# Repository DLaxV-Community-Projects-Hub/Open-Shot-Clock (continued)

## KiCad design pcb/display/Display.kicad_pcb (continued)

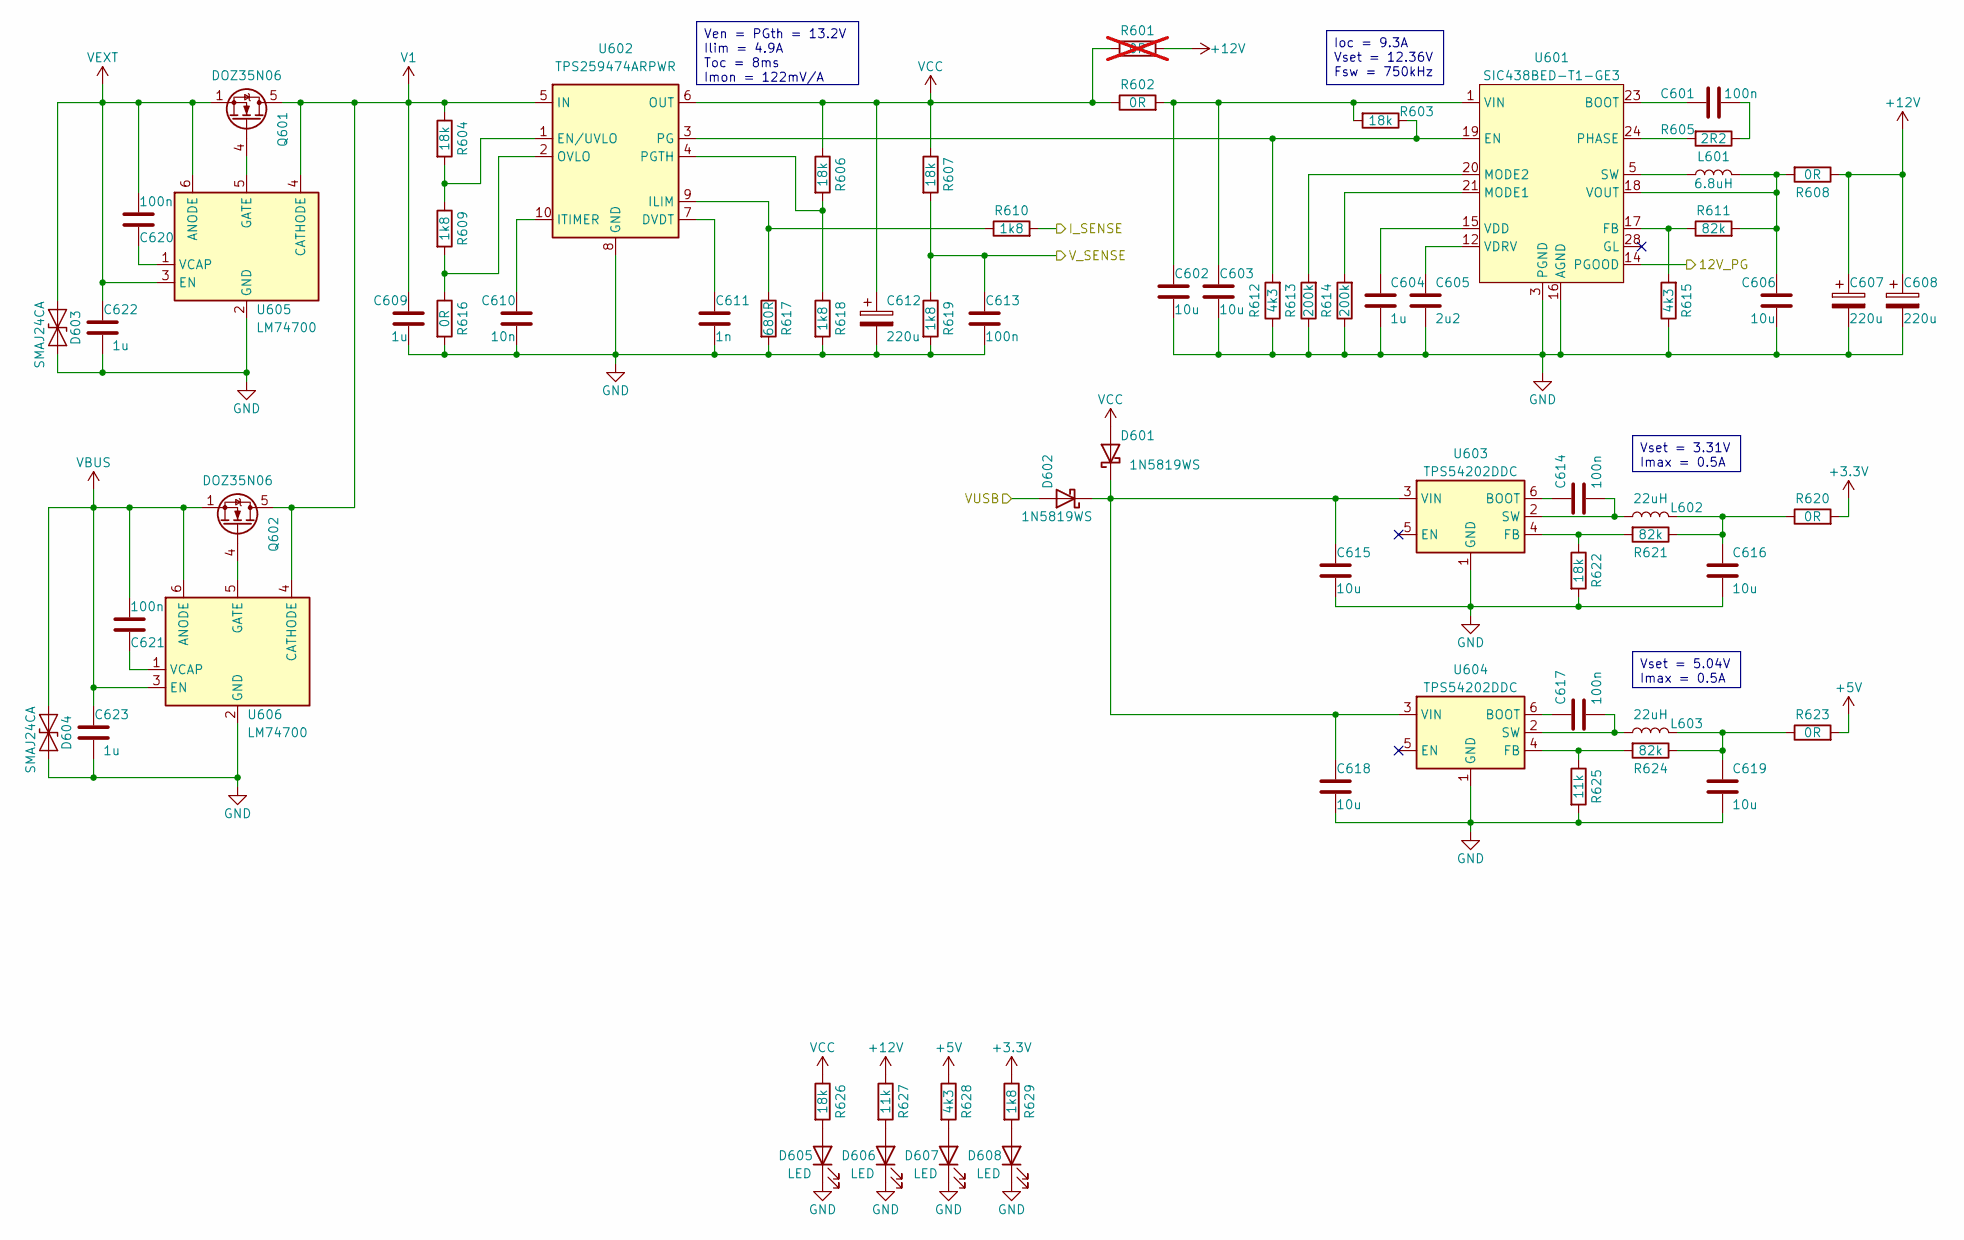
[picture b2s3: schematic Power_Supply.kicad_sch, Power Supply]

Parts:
C601, C613, C614, C617, C620, C621: 100n; C_0402_1005Metric; LCSC Part # C307331
C602, C603, C606, C615, C618: 10u; C_1206_3216Metric; LCSC Part # C13585
C604, C609, C622, C623: 1u; C_0603_1608Metric; LCSC Part # C15849
C605: 2u2; C_0603_1608Metric; LCSC Part # C23630
C607, C608, C612: 220u; CP_Elec_8x10; LCSC Part # C5246542
C610: 10n; C_0402_1005Metric; LCSC Part # C15195
C611: 1n; C_0402_1005Metric; LCSC Part # C1523
C616, C619: 10u; C_0603_1608Metric; LCSC Part # C19702
D601, D602: 1N5819WS; D_SOD-323; LCSC Part # C191023
D603, D604: SMAJ24CA; D_SMA; LCSC Part # C20883150
D605, D606, D607, D608: LED; LED_0603_1608Metric; LCSC Part # C2286
L601: 6.8uH; L_Bourns_SRP1050WA; LCSC Part # C32712978
L602, L603: 22uH; L_Changjiang_FNR4030S; LCSC Part # C206327
Q601, Q602: DOZ35N06; VSON-8_3.3x3.3mm_P0.65mm_Custom; LCSC Part # C36499167
R601: 0R; R_1206_3216Metric; not fitted
R602, R608: 0R; R_1206_3216Metric
R603, R604, R606, R607, R622, R626: 18k; R_0402_1005Metric
R605: 2R2; R_0402_1005Metric
R609, R610, R618, R619, R629: 1k8; R_0402_1005Metric
R611, R621, R624: 82k; R_0402_1005Metric
R612, R615, R628: 4k3; R_0402_1005Metric
R613, R614: 200k; R_0402_1005Metric
R616: 0R; R_0402_1005Metric
R617: 680R; R_0402_1005Metric
R620, R623: 0R; R_0603_1608Metric
R625, R627: 11k; R_0402_1005Metric
U601: SIC438BED-T1-GE3; Vishay_PowerPAK_MLP44-24L_ThermalVias; LCSC Part # C511430
U602: TPS259474ARPWR; RPW0010A_VQFN-HR-10; LCSC Part # C3662807
U603, U604: TPS54202DDC; SOT-23-6; LCSC Part # C191884
U605, U606: LM74700; SOT-23-6; LCSC Part # C2941042

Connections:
+3.3V: R620.2, R629.1; also elsewhere on the board
+5V: R623.2, R628.1; also elsewhere on the board
+12V: C607.1, C608.1, R601.2, R608.1, R627.1; also elsewhere on the board
/12V_PG: U601.14 (PGOOD); also elsewhere on the board
/I_SENSE: R610.2; also elsewhere on the board
/Power Supply/VUSB: D602.2 (A); also elsewhere on the board
/V_SENSE: C613.2, R607.2, R619.1; also elsewhere on the board
GND: C602.2, C603.2, C604.2, C605.2, C606.2, C607.2, C608.2, C609.1, C610.1, C611.1, C612.2, C613.1, C615.2, C616.2, C618.2, C619.2, C622.2, C623.2, D603.2 (A2), D604.2 (A2), D605.1 (K), D606.1 (K), D607.1 (K), D608.1 (K), R612.1, R613.1, R614.1, R615.1, R616.2, R617.2, R618.2, R619.2, R622.2, R625.2, U601.3 (PGND), U601.4 (PGND), U601.13 (PGND), U601.16 (AGND), U601.25 (AGND), U601.27 (PGND), U602.8 (GND), U603.1 (GND), U604.1 (GND), U605.2 (GND), U606.2 (GND); also elsewhere on the board
unnamed: C601.2, R605.1
unnamed: C616.1, L602.2, R620.1, R621.1
unnamed: C619.1, L603.2, R623.1, R624.1
unnamed: C615.1, C618.1, D601.1 (K), D602.1 (K), U603.3 (VIN), U604.3 (VIN)
unnamed: D605.2 (A), R626.2
unnamed: D606.2 (A), R627.2
unnamed: D607.2 (A), R628.2
unnamed: D608.2 (A), R629.2
unnamed: Q601.4 (G), U605.5 (GATE)
unnamed: Q602.4 (G), U606.5 (GATE)
unnamed: C601.1, U601.23 (BOOT)
unnamed: R603.1, R612.2, U601.19 (EN), U602.3 (PG)
unnamed: R611.1, R615.2, U601.17 (FB)
unnamed: R614.2, U601.21 (MODE1)
unnamed: R613.2, U601.20 (MODE2)
unnamed: R605.2, U601.24 (PHASE)
unnamed: C604.1, U601.15 (VDD)
unnamed: C605.1, U601.12 (VDRV)
unnamed: C606.1, L601.2, R608.2, R611.2, U601.18 (VOUT)
unnamed: C611.2, U602.7 (DVDT)
unnamed: R604.2, R609.1, U602.1 (EN/UVLO)
unnamed: R610.1, R617.1, U602.9 (ILIM)
unnamed: C610.2, U602.10 (ITIMER)
unnamed: R609.2, R616.1, U602.2 (OVLO)
unnamed: R606.2, R618.1, U602.4 (PGTH)
unnamed: C614.1, U603.6 (BOOT)
unnamed: R621.2, R622.1, U603.4 (FB)
unnamed: C614.2, L602.1, U603.2 (SW)
unnamed: C617.1, U604.6 (BOOT)
unnamed: R624.2, R625.1, U604.4 (FB)
unnamed: C617.2, L603.1, U604.2 (SW)
unnamed: C620.2, U605.1 (VCAP)
unnamed: C621.2, U606.1 (VCAP)
SW: L601.1, U601.5 (SW), U601.6 (SW), U601.7 (SW), U601.8 (SW), U601.9 (SW)
V1: C609.2, Q601.5 (D), Q602.5 (D), R604.1, U602.5 (IN), U605.4 (CATHODE), U606.4 (CATHODE)
VBUS: C621.1, C623.1, D604.1 (A1), Q602.1 (S), Q602.2 (S), Q602.3 (S), U606.3 (EN), U606.6 (ANODE); also elsewhere on the board
VCC: C612.1, D601.2 (A), R601.1, R602.1, R606.1, R607.1, R626.1, U602.6 (OUT); also elsewhere on the board
VEXT: C620.1, C622.1, D603.1 (A1), Q601.1 (S), Q601.2 (S), Q601.3 (S), U605.3 (EN), U605.6 (ANODE); also elsewhere on the board
VIN: C602.1, C603.1, R602.2, R603.2, U601.1 (VIN), U601.2 (VIN), U601.22 (VIN), U601.26 (VIN)

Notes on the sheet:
Vset = 3.31V Imax = 0.5A
Ven = PGth = 13.2V Ilim = 4.9A Toc = 8ms Imon = 122mV/A
Vset = 5.04V Imax = 0.5A
Ioc = 9.3A Vset = 12.36V Fsw = 750kHz

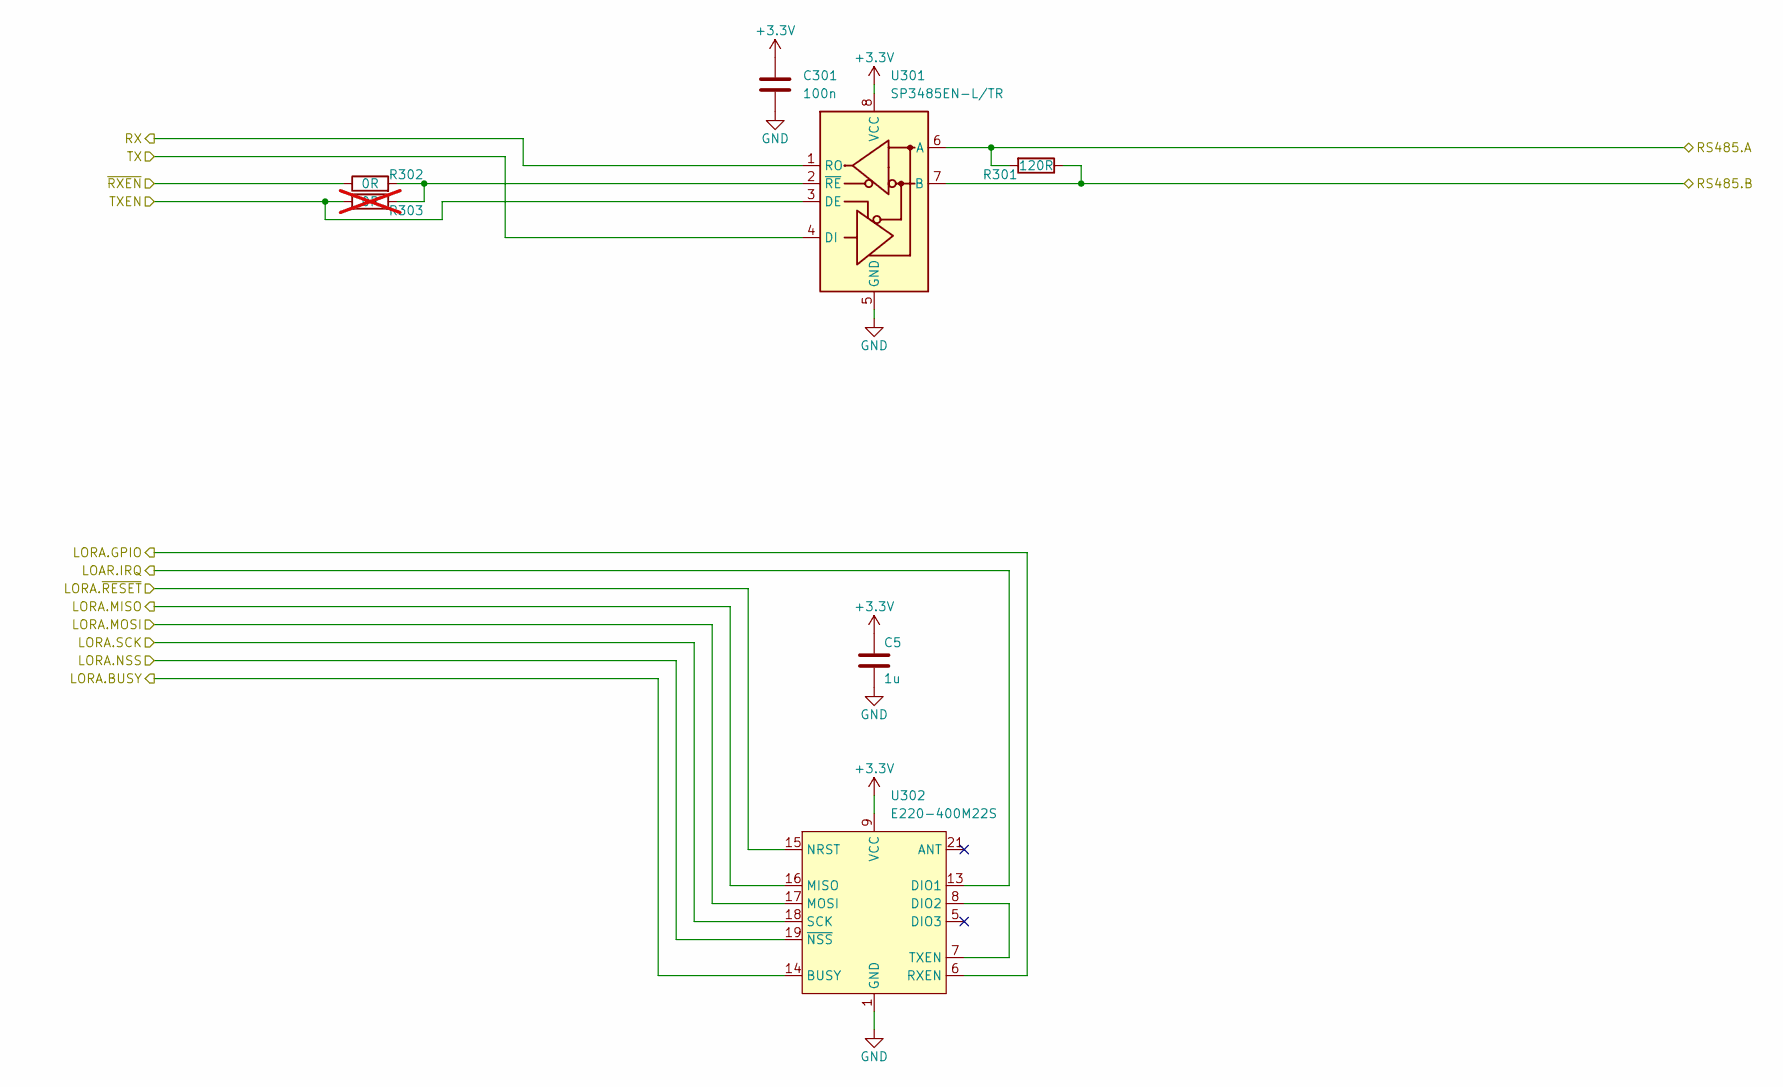
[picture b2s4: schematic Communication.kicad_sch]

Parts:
C5: 1u; C_0402_1005Metric; LCSC Part # C52923
C301: 100n; C_0402_1005Metric; LCSC Part # C307331
R301: 120R; R_0805_2012Metric
R302: 0R; R_0603_1608Metric
R303: 0R; R_0603_1608Metric; not fitted
U301: SP3485EN-L/TR; SOIC-8_3.9x4.9mm_P1.27mm; LCSC Part # C8963
U302: E220-400M22S; LCSC Part # C2971737

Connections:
+3.3V: C5.1, C301.1, U301.8 (VCC), U302.9 (VCC); also elsewhere on the board
/Communication/RS485.A: R301.2, U301.6 (A); also elsewhere on the board
/Communication/RS485.B: R301.1, U301.7 (B); also elsewhere on the board
/LORA.BUSY: U302.14 (BUSY); also elsewhere on the board
/LORA.DIO1: U302.6 (RXEN); also elsewhere on the board
/LORA.IRQ: U302.13 (DIO1); also elsewhere on the board
/LORA.NSS: U302.19 (~NSS); also elsewhere on the board
/LORA.RST: U302.15 (NRST); also elsewhere on the board
/SPI.CLK: U302.18 (SCK); also elsewhere on the board
/SPI.MISO: U302.16 (MISO); also elsewhere on the board
/SPI.MOSI: U302.17 (MOSI); also elsewhere on the board
/UART.RX: U301.1 (RO); also elsewhere on the board
/UART.TX: U301.4 (DI); also elsewhere on the board
/UART.TXEN: R303.1, U301.3 (DE); also elsewhere on the board
/UART.~RXEN: R302.1; also elsewhere on the board
GND: C5.2, C301.2, U301.5 (GND), U302.1 (GND), U302.2 (GND), U302.3 (GND), U302.4 (GND), U302.10 (GND), U302.11 (GND), U302.12 (GND), U302.20 (GND), U302.22 (GND); also elsewhere on the board
unnamed: R302.2, R303.2, U301.2 (~RE)
unnamed: U302.7 (TXEN), U302.8 (DIO2)

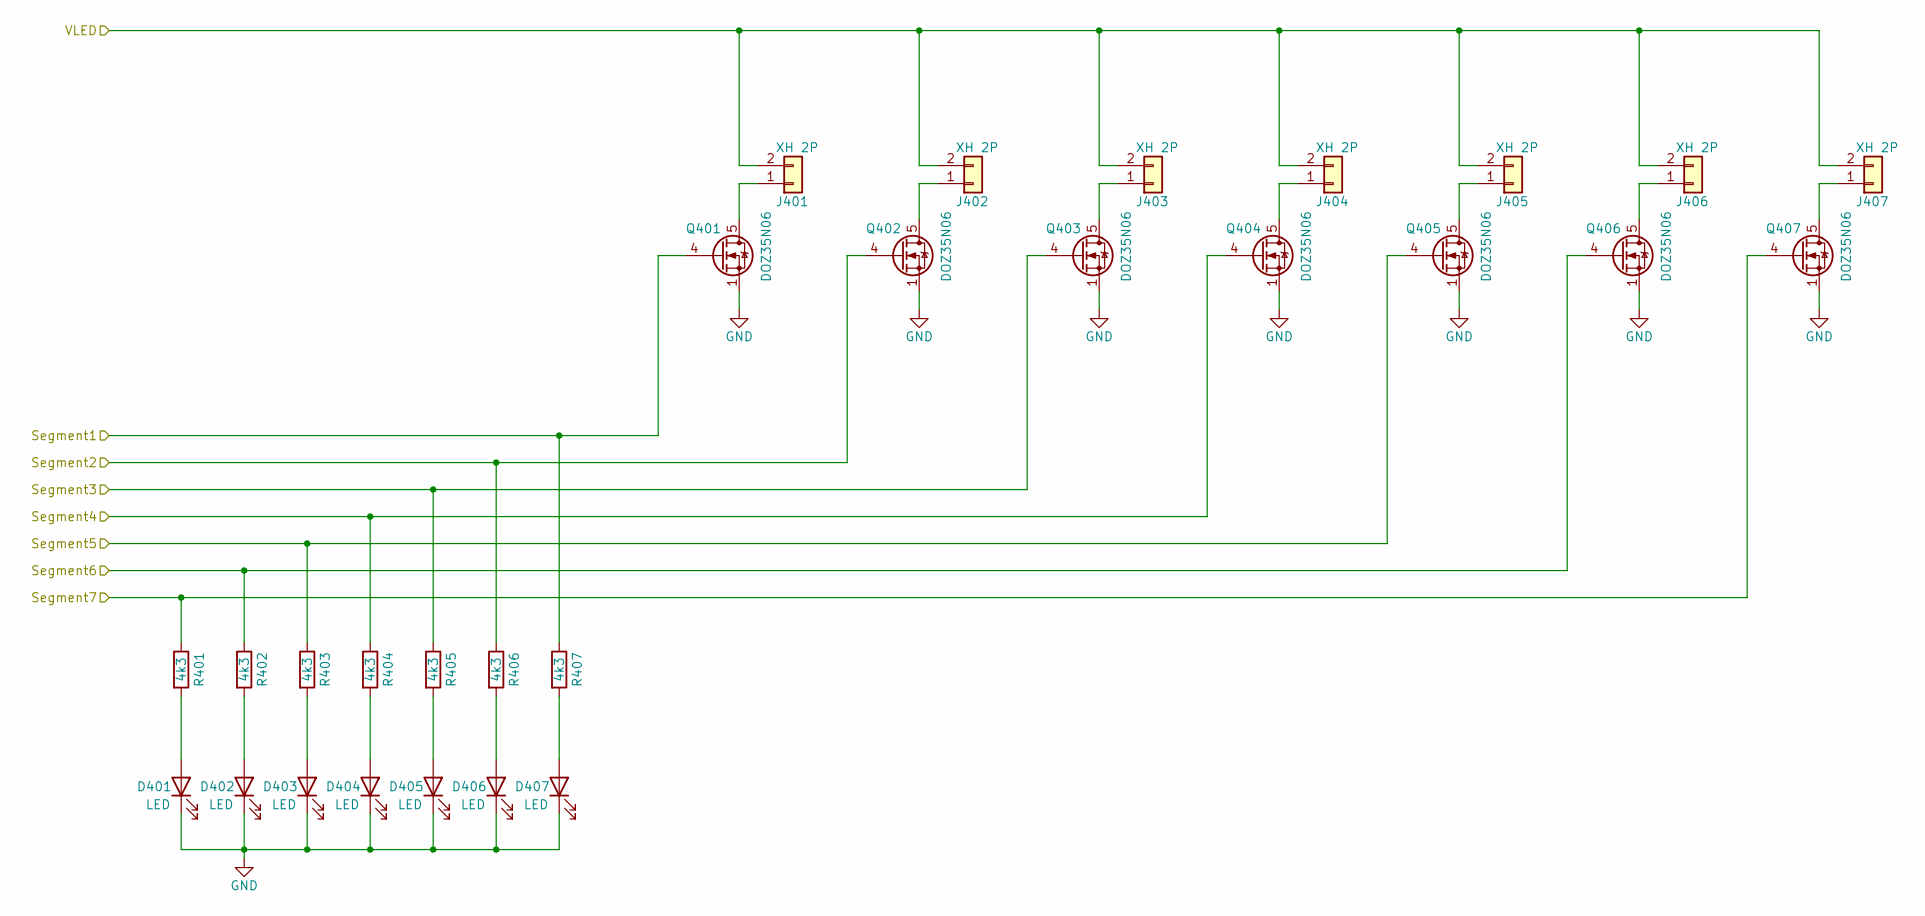
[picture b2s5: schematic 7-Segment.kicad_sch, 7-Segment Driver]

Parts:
D401, D402, D403, D404, D405, D406, D407: LED; LED_0603_1608Metric; LCSC Part # C2286
J401, J402, J403, J404, J405, J406, J407: XH 2P; JST_XH_B2B-XH-A_1x02_P2.50mm_Vertical; LCSC Part # C158012
Q401, Q402, Q403, Q404, Q405, Q406, Q407: DOZ35N06; VSON-8_3.3x3.3mm_P0.65mm_Custom; LCSC Part # C36499167
R401, R402, R403, R404, R405, R406, R407: 4k3; R_0402_1005Metric

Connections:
+12V: J401.2, J402.2, J403.2, J404.2, J405.2, J406.2, J407.2; also elsewhere on the board
/LED Driver/7-Segment1 units/Segment1: Q401.4 (G), R407.1; also elsewhere on the board
/LED Driver/7-Segment1 units/Segment2: Q402.4 (G), R406.1; also elsewhere on the board
/LED Driver/7-Segment1 units/Segment3: Q403.4 (G), R405.1; also elsewhere on the board
/LED Driver/7-Segment1 units/Segment4: Q404.4 (G), R404.1; also elsewhere on the board
/LED Driver/7-Segment1 units/Segment5: Q405.4 (G), R403.1; also elsewhere on the board
/LED Driver/7-Segment1 units/Segment6: Q406.4 (G), R402.1; also elsewhere on the board
/LED Driver/7-Segment1 units/Segment7: Q407.4 (G), R401.1; also elsewhere on the board
GND: D401.1 (K), D402.1 (K), D403.1 (K), D404.1 (K), D405.1 (K), D406.1 (K), D407.1 (K), Q401.1 (S), Q401.2 (S), Q401.3 (S), Q402.1 (S), Q402.2 (S), Q402.3 (S), Q403.1 (S), Q403.2 (S), Q403.3 (S), Q404.1 (S), Q404.2 (S), Q404.3 (S), Q405.1 (S), Q405.2 (S), Q405.3 (S), Q406.1 (S), Q406.2 (S), Q406.3 (S), Q407.1 (S), Q407.2 (S), Q407.3 (S); also elsewhere on the board
unnamed: D401.2 (A), R401.2
unnamed: D402.2 (A), R402.2
unnamed: D403.2 (A), R403.2
unnamed: D404.2 (A), R404.2
unnamed: D405.2 (A), R405.2
unnamed: D406.2 (A), R406.2
unnamed: D407.2 (A), R407.2
unnamed: J401.1, Q401.5 (D)
unnamed: J402.1, Q402.5 (D)
unnamed: J403.1, Q403.5 (D)
unnamed: J404.1, Q404.5 (D)
unnamed: J405.1, Q405.5 (D)
unnamed: J406.1, Q406.5 (D)
unnamed: J407.1, Q407.5 (D)

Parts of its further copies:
D501, D502, D503, D504, D505, D506, D507: LED; LED_0603_1608Metric; LCSC Part # C2286
J501, J502, J503, J504, J505, J506, J507: XH 2P; JST_XH_B2B-XH-A_1x02_P2.50mm_Vertical; LCSC Part # C158012
Q501, Q502, Q503, Q504, Q505, Q506, Q507: DOZ35N06; VSON-8_3.3x3.3mm_P0.65mm_Custom; LCSC Part # C36499167
R501, R502, R503, R504, R505, R506, R507: 4k3; R_0402_1005Metric

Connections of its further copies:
+12V: J501.2, J502.2, J503.2, J504.2, J505.2, J506.2, J507.2; also elsewhere on the board
/LED Driver/7-Segment2 tens/Segment1: Q501.4 (G), R507.1; also elsewhere on the board
/LED Driver/7-Segment2 tens/Segment2: Q502.4 (G), R506.1; also elsewhere on the board
/LED Driver/7-Segment2 tens/Segment3: Q503.4 (G), R505.1; also elsewhere on the board
/LED Driver/7-Segment2 tens/Segment4: Q504.4 (G), R504.1; also elsewhere on the board
/LED Driver/7-Segment2 tens/Segment5: Q505.4 (G), R503.1; also elsewhere on the board
/LED Driver/7-Segment2 tens/Segment6: Q506.4 (G), R502.1; also elsewhere on the board
/LED Driver/7-Segment2 tens/Segment7: Q507.4 (G), R501.1; also elsewhere on the board
GND: D501.1 (K), D502.1 (K), D503.1 (K), D504.1 (K), D505.1 (K), D506.1 (K), D507.1 (K), Q501.1 (S), Q501.2 (S), Q501.3 (S), Q502.1 (S), Q502.2 (S), Q502.3 (S), Q503.1 (S), Q503.2 (S), Q503.3 (S), Q504.1 (S), Q504.2 (S), Q504.3 (S), Q505.1 (S), Q505.2 (S), Q505.3 (S), Q506.1 (S), Q506.2 (S), Q506.3 (S), Q507.1 (S), Q507.2 (S), Q507.3 (S); also elsewhere on the board
unnamed: D501.2 (A), R501.2
unnamed: D502.2 (A), R502.2
unnamed: D503.2 (A), R503.2
unnamed: D504.2 (A), R504.2
unnamed: D505.2 (A), R505.2
unnamed: D506.2 (A), R506.2
unnamed: D507.2 (A), R507.2
unnamed: J501.1, Q501.5 (D)
unnamed: J502.1, Q502.5 (D)
unnamed: J503.1, Q503.5 (D)
unnamed: J504.1, Q504.5 (D)
unnamed: J505.1, Q505.5 (D)
unnamed: J506.1, Q506.5 (D)
unnamed: J507.1, Q507.5 (D)

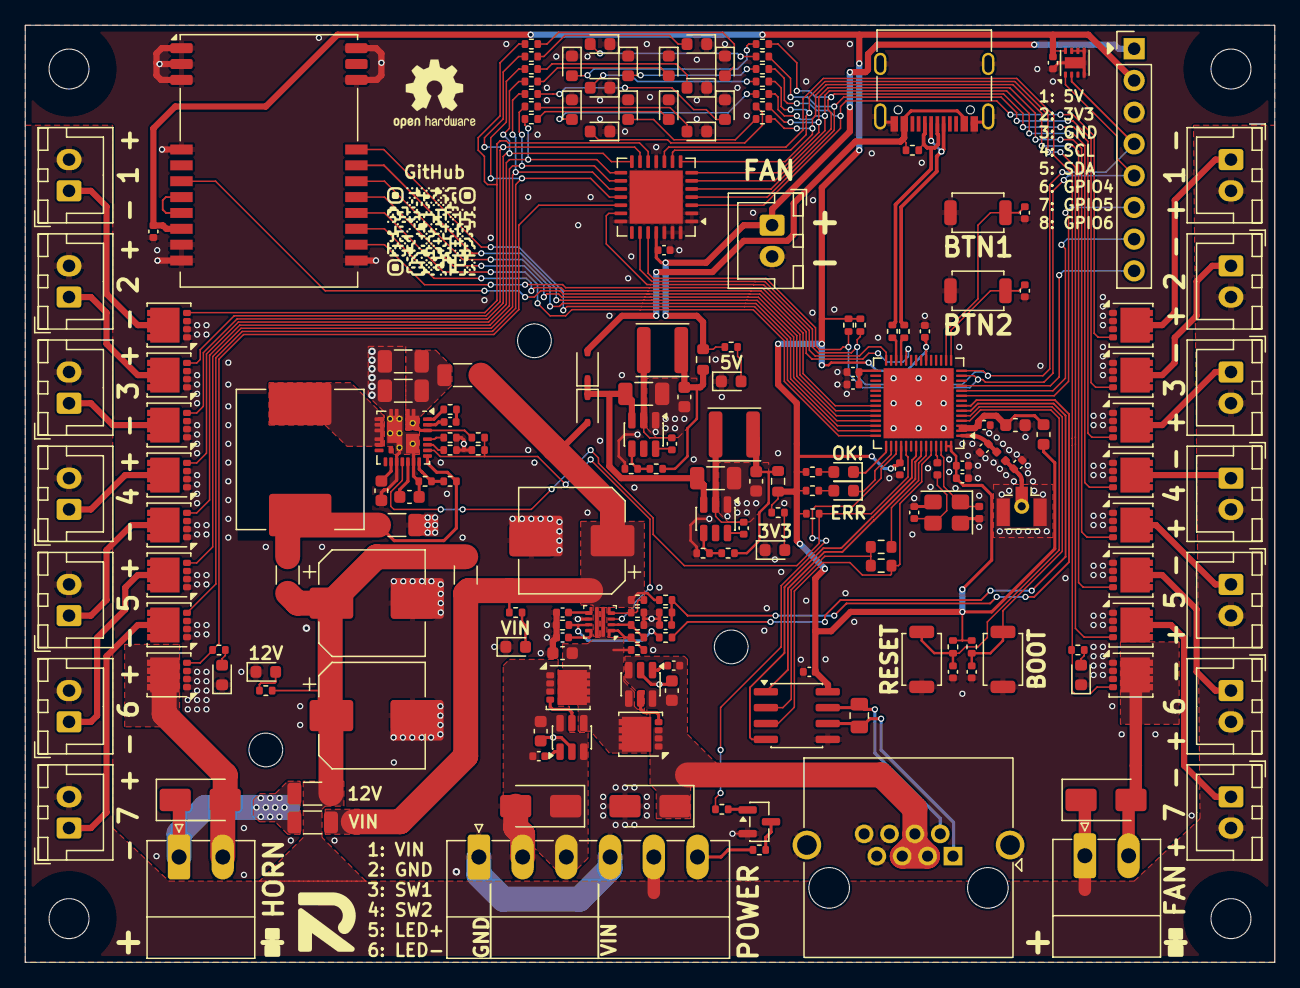
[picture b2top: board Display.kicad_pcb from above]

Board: 2 copper layers, 100.0 x 75.0 mm, 205 parts (1 on the bottom side), 141 nets.

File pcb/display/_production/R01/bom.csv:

Designator,Footprint,Quantity,Value,LCSC Part #
"C101, C102, C103, C104, C105, C201, C301, C601, C613, C614, C617, C620, C621",0402,13,100n,
"C602, C603, C606, C615, C618",1206,5,10u,
"C604, C609, C622, C623",0603,4,1u,
C605,0603,1,2u2,
"C607, C608, C612",CP_Elec_8x10,3,150u,
C610,0402,1,10n,
C611,0402,1,1n,
"C616, C619",0603,2,10u,
"D101, D102, D201, D203, D401, D402, D403, D404, D405, D406, D407, D501, D502, D503, D504, D505, D506, D507, D605, D606, D607, D608",0603,22,LED,
"D202, D204",D_SMA,2,SS54,
"D601, D602",D_SOD-323,2,1N5819WS,
"D603, D604",D_SMA,2,SMAJ24CA,
J101,RJ45_Amphenol_RJHSE5380,1,RJ45,
J102,"PhoenixContact_MC_1,5_6-G-3.5_1x06_P3.50mm_Horizontal",1,Screw Terminal 3.5mm,
J103,PinHeader_1x08_P2.54mm_Vertical,1,01x08_Pin,
"J201, J202","PhoenixContact_MC_1,5_2-G-3.5_1x02_P3.50mm_Horizontal",2,Term 3.5mm,
"J401, J402, J403, J404, J405, J406, J407, J501, J502, J503, J504, J505, J506, J507",JST_XH_B2B-XH-A_1x02_P2.50mm_Vertical,14,XH 2P,
L601,L_Bourns_SRP1050WA,1,6.8uH,
"L602, L603",L_Changjiang_FNR4030S,2,33uH,
P101,USB_C_Receptacle_G-Switch_GT-USB-7010ASV,1,USB_C_Plug_USB2.0,
Q101,SOT-23,1,2N7002,
"Q201, Q202, Q401, Q402, Q403, Q404, Q405, Q406, Q407, Q501, Q502, Q503, Q504, Q505, Q506, Q507, Q601, Q602",VSON-8_3.3x3.3mm_P0.65mm_NexFET,18,DOZ35N06,
"R101, R102, R104, R105, R106, R109, R609, R610, R618, R619, R629",0402,11,1k8,
"R107, R108, R203, R204, R401, R402, R403, R404, R405, R406, R407, R501, R502, R503, R504, R505, R506, R507, R612, R615, R628",0402,21,4k3,
"R110, R603, R604, R606, R607, R622, R626",0402,7,18k,
"R202, R602, R608",1206,3,0R,
R301,0805,1,120R,
"R302, R620, R623",0603,3,0R,
R605,0402,1,2R2,
"R611, R621, R624",0402,3,82k,
"R613, R614",0402,2,200k,
R616,0402,1,0R,
R617,0402,1,680R,
"R625, R627",0402,2,11k,
"SW101, SW102, SW103, SW104",SW_Push_4x3mm,4,SW_4x3mm,
U101,WSON-8-1EP_2x2mm_P0.5mm_EP0.9x1.6mm,1,TMP1075DSGR,
U102,ESP32-S3-MINI-1U,1,ESP32-S3-MINI-1U-N8,
U201,QFN-28-1EP_6x6mm_P0.65mm_EP4.25x4.25mm,1,PCA9685BS,
U301,SOIC-8_3.9x4.9mm_P1.27mm,1,SP3485EN-L/TR,
U302,E220-400M22S,1,E220-400M22S,
U601,Vishay_PowerPAK_MLP44-24L_ThermalVias,1,SIC438BED-T1-GE3,
U602,RPW0010A_VQFN-HR-10,1,TPS259474ARPWR,
"U603, U604",SOT-23-6,2,TPS54202DDC,
"U605, U606",SOT-23-6,2,LM74700,

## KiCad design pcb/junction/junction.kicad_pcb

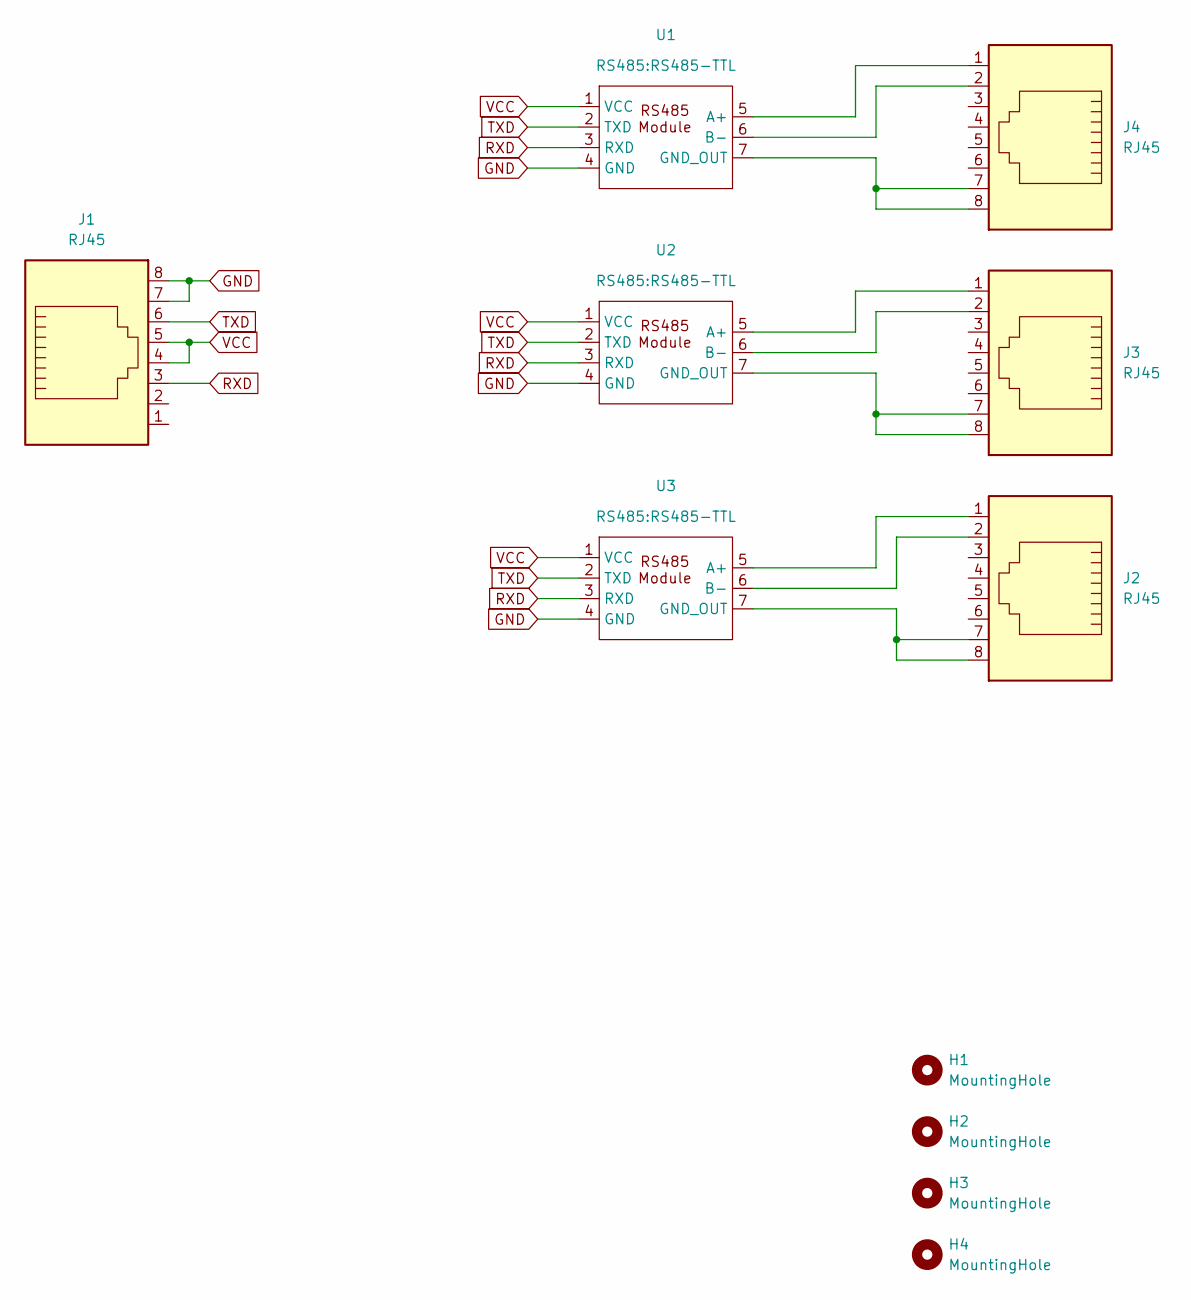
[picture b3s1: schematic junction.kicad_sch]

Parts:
H1, H2, H3, H4: MountingHole; MountingHole_3.2mm_M3
J1, J2, J3, J4: RJ45; RJ45_Amphenol_54602-x08_Horizontal
U1, U2, U3: RS485-TTL

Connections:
GND: J1.7, J1.8, U1.4 (GND), U2.4 (GND), U3.4 (GND)
unnamed: J4.1, U1.5 (A+)
unnamed: J4.2, U1.6 (B-)
unnamed: J4.7, J4.8, U1.7 (GND_OUT)
unnamed: J3.1, U2.5 (A+)
unnamed: J3.2, U2.6 (B-)
unnamed: J3.7, J3.8, U2.7 (GND_OUT)
unnamed: J2.1, U3.5 (A+)
unnamed: J2.2, U3.6 (B-)
unnamed: J2.7, J2.8, U3.7 (GND_OUT)
RXD: J1.3, U1.3 (RXD), U2.3 (RXD), U3.3 (RXD)
TXD: J1.6, U1.2 (TXD), U2.2 (TXD), U3.2 (TXD)
VCC: J1.4, J1.5, U1.1 (VCC), U2.1 (VCC), U3.1 (VCC)

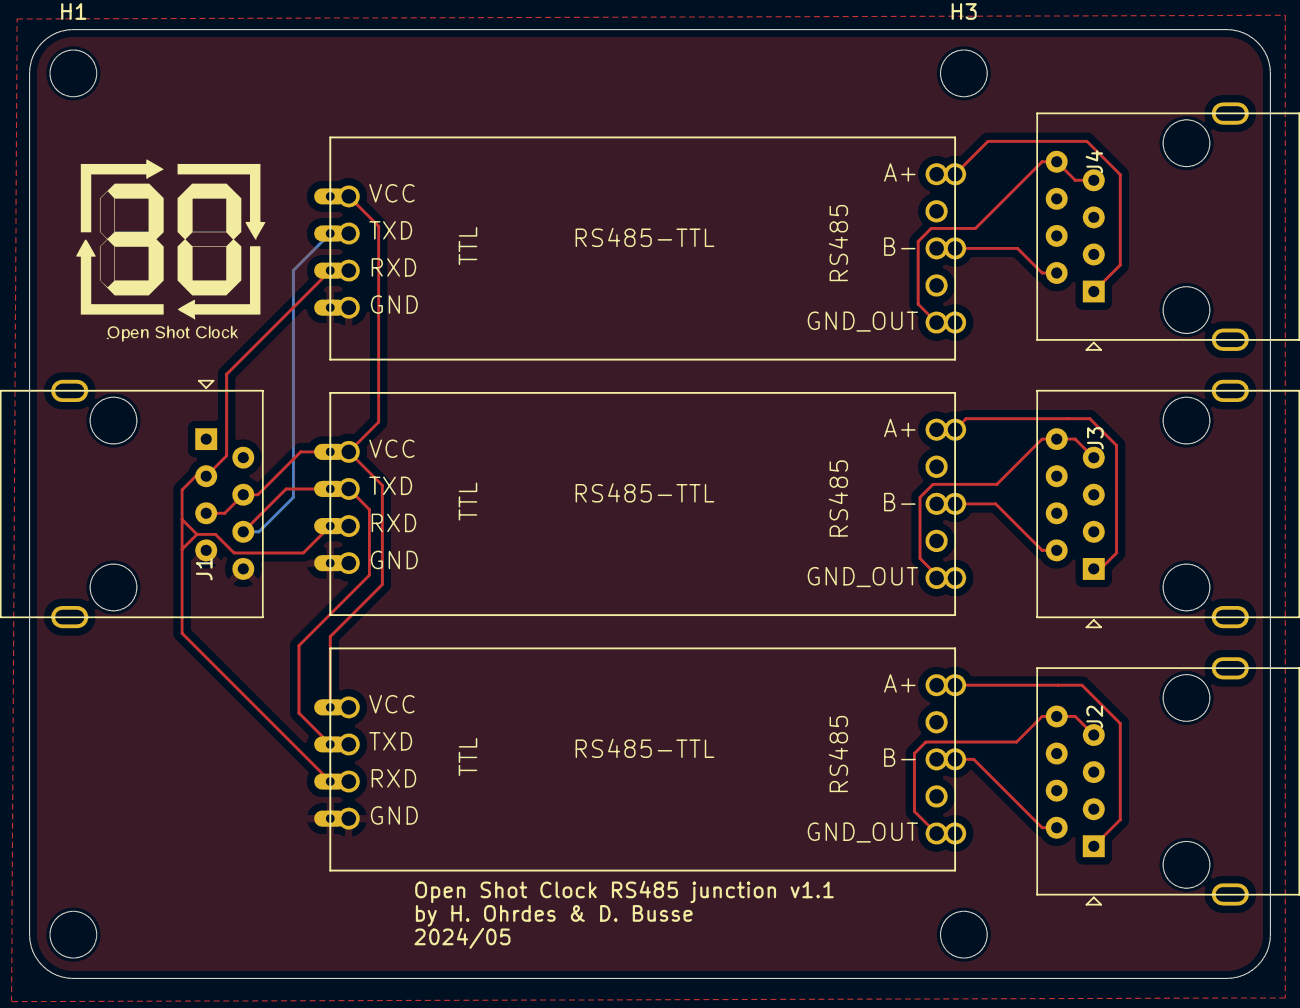
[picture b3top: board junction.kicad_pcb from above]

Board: 2 copper layers, 85.0 x 65.0 mm, 11 parts (0 on the bottom side), 13 nets.

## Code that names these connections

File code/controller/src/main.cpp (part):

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
buttonStates_t buttonState = NONE;

Button btn1(PIN_B1), // define the button
    btn2(PIN_B2),
    btn3(PIN_B3),
    btn4(PIN_B4),
    btn5(PIN_B5),
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    pinMode(PIN_PWR, OUTPUT);
    digitalWrite(PIN_PWR, HIGH);
    ESP_LOGE("Init", "As OSC R1"); 
    pinMode(V_SENSE, ANALOG);
    pinMode(I_SENSE, ANALOG);
    pinMode(LED_ERR, OUTPUT);
    pinMode(PIN_HORN, OUTPUT);
    pinMode(UART_TXEN, OUTPUT);
    digitalWrite(UART_TXEN, HIGH);
    spi.begin(LoRa_CLK, LoRa_MISO, LoRa_MOSI, LoRa_NSS);
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
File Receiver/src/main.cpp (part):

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  ware to OLED's reset pin, the low-level signal at least 5ms.

  OLED pins to ESP32 GPIOs via this connecthin:
  OLED_SDA -- GPIO4
  OLED_SCL -- GPIO15
  OLED_RST -- GPIO16
  
  by Aaron.Lee from HelTec AutoMation, ChengDu, China
  成都惠利特自动化科技有限公司
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#define RXD2 13
#define TXD2 12

#define Vext 21

String inputString = "";         // a String to hold incoming data
bool stringComplete = false;  // whether the string is complete
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
void setup() {

  //pinMode(Vext,OUTPUT);
  
  //digitalWrite(Vext, HIGH);

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
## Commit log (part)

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2021-08-31 Ordner mit Temp_Monitor_Version hinzugefügt
2021-09-13 sender aktualisiert - starte Bereinigung
2021-09-13 Aufgeräumt-OTA-OLED_Display_Update-Kanal_Wahl_Web_Server-Temp_Sensor_raus
2021-09-27 Function_display-Display_aus_wenn_Smartphone_Steuerung
2021-09-27 3_sec_Press_Reset_with_Stop
2021-10-15 Display aus wenn Steuerung per Smartphone bug fix
2021-12-14 port to VS code
2021-12-15 updated_design_on_channel_selection_sender_and_receiver
2021-12-15 updated_design_on_channel_selection_sender_and_receiver (#3)
2022-01-21 Set tx power to 9 - test positiv (#4)
2022-01-21 added settings page with brightness control
2022-01-21 deleted not needed variables
2022-02-08 styled settings page and select element
2022-02-09 again
2022-02-09 updated sender button pin-out/wifi new controller
2022-03-25 unwantedRecs
2022-03-25 Integrated 3 versions
2022-03-25 fixed send command
2022-03-29 added console info when fan starts/stops
2022-03-29 Test positiv - both
2022-04-13 Button_Layout_Changeed_to_Controller_V2.1
2022-05-14 added_Hannover_Clock_to_Wifi_Options
2022-06-03 corrected pin out discription reset and cancel
2022-06-03 integratedt serial2 for rs485 test
2022-06-14 positiv rs485 test
2022-07-27 added 2 Buttons, minor refactoring
2022-07-27 added DS_Store to gitignore
2022-07-27 updated async webserver to fix bug with current esp tools
2022-09-30 implement rs 485 communication (#22)
    * Initial base (#2)
    * initial commit
    * Ordner mit Temp_Monitor_Version hinzugefügt
    * sender aktualisiert - starte Bereinigung
    * Aufgeräumt-OTA-OLED_Display_Update-Kanal_Wahl_Web_Server-Temp_Sensor_raus
    * sender_OTA_und_Kanalwahl-Display_OLED_Design_und_Connecting_Funktion
2022-12-23 renamed Sender/Receiver to Controller/Display
2023-01-02 added pcb files
2023-01-02 refactores folder structure
2023-01-02 added logo to assets
2023-01-02 Update README.md
    added Usage
2023-02-17 Add files via upload
    updated some costs and links
    changed ethernet socket product
2023-03-31 Add files via upload
    added new named images again
2023-03-31 Update README.md
    changed image naming from *.svg to *.pptx.svg
2023-03-31 Create README.md
    added design option 8 mm thick base plate
2023-03-31 Add files via upload
    added mark for 5 mm drilling hole (antenna)
2023-03-31 Add files via upload
    - added 8 mm base plate option flange design parts
    - updated tripod flange design to solve issue #23
    - added horn cuff clip to solve issue #23
2023-03-31 Update README.md
    typo
2023-04-04 swithed webserver dependency to use HTTPS instead of SSH
2023-04-05 Update README.md
    changed to assets readme.md
2023-04-05 deleted unnecessary files
2023-04-05 Update README.md
    changed theme image link to new assets branch
2023-04-05 updated theme with 3d-printing corner joint
2023-04-05 updated cad and documentation files
2023-04-06 updated sourcing-list and instructions
2023-04-06 Dev (#32)
    * manually merged refactoring branch (issue 6)
    * swithed webserver dependency to use HTTPS instead of SSH
    * swithed webserver dependency to use HTTPS instead of SSH
    * deleted assets folder and changed config
    * Update README.md
    changed theme image link to new assets branch
2023-10-02 initial test
2023-10-20 switched to RadioLib to be able to use heltec v3. Added heltec_wifi_lora_32_V3 env. Added v3 pin configs. Still WIP
2023-10-20 switched to RadioLib to be able to use heltec v3. Added heltec_wifi_lora_32_V3 env. Added v3 pin configs. For display. Still WIP
2023-11-02 added V3 infos to README
2023-11-02 minor cleaning
2023-11-02 refactored controller platformio.ini
2023-11-06 added I2C handling for different boards. Added PCB config to choose PCB
2023-11-06 cleanup
2023-11-06 removed twowire object for V2 when used with OLED_I2C, bc didn't work
2024-01-03 added v3 mod image to readme
2024-01-05 added 5V mod
2024-01-25 added dewarp files for abs/asa prints
2024-02-12 refactored pin and board config
2024-02-23 added higher controller
2024-03-04 added option to reset to different times, refactored button handling
2024-03-10 added reset on conntecion lost
2024-03-10 changed wifi name for display
2024-03-11 changed channels to use syncword instead of band
2024-03-11 changed config, removed ESP.restart
2024-03-11 changed channel to use syncword for controller + refactoring
2024-03-12 config cleanup
2024-03-12 removed prints
2024-03-13 fixed platform version
2024-03-17 added frequency to channel, so it uses different frequency and sync words
2024-04-13 Feature/make channels work (#37)
    * added frequency to channel, so it uses different frequency and sync words
    * added channel to message, added message validation
2024-05-17 fixed crashing display (lora restart on fail), fixed OLED mode display
2024-05-21 added versions page for display
2024-05-22 added versions for controller
2024-05-22 17 displays and controller firmware version not visible (#48)
    * added versions page for display
    * added versions for controller
2024-05-22 fixed bug, brightnesslevel now using exact string position from message
2024-05-25 config?
2024-05-30 fixed bug for RS485 communication (there is an extra whitespace sent, that crashed validation)
2024-05-30 junction v1.1 PCB in kicad (#52)
2024-05-30 added controller v2.1 in kicad
2024-05-31 changed extra holes in junction to be THT to make them manufacturable
2024-06-13 added controller V2.1
2024-06-13 fixed wrong pcb version error
2024-08-08 fixed controller by updating lib_deps / added build_flag for async webserver async-mode / updated main for ElegantOTA
2024-08-18 further Tests on receive delay - 1 sec plus delay without peripheral - little delay with peripheral
2024-11-17 Final Version of Prototype Rev. 00
    Switched back to PCA9685 for PWM, removed high side switch
    Updated some component values
2024-12-09 add new controller and junction case, add looser horn cuff model
2025-02-15 Final Version of new Controller Rev. 00 (Prototype)
2025-02-15 Add BOM files and adjust gitignore to not exclude BOMs
2025-02-17 Added support for new custom display hardware
    Removed Heltec library
    Implemented OLED display using Adafruit library
    Increased RadioLib version as bugs for LLCC68 where fixed
2025-02-19 prevent resetTime to be over 99 or unter 0
2025-02-19 refactor: rename vars, remove vars, stop turning off display on wifi control, bc it works
2025-02-19 refactoring: renaming, sorting
2025-02-20 refactor count function and variable names
2025-02-20 refactor: moving functions
2025-02-20 refactor: rename button variables and state for consistency
2025-02-20 Chore/refactor button handling (#55)
2025-02-20 Prepare release v1.2.0 (#56)
    - add heltec v3 compatibility
    - add version endpoint
    - add new controller PCB using kicad
    - update junction PCB using kicad
    - change lora communication, new channel system
    - cad updates, new controller, junction case, horn cuff, anti-warp corners
2025-02-21 feat: add git tag information to versioning in display and controller modules
2025-02-21 Prepare release v1.2.1 (#57)
    * feat: add git tag information to versioning in display and controller modules
2025-02-23 Added ReleaseNotes for Display
    Deleted old files
2025-03-30 Revision 01 of Controller hardware
    - fixed bugs from revision 00
    - changed folder structure
    - added ReleaseNotes_Controller.md to keep track of changes
2025-04-08 Display HW Revision 01
2025-04-09 Final adjustments and BOM optimization
2025-04-11 Update wrong values after import in JLC for production
2025-05-03 Update component values after feedback from JLC
2025-05-11 Updated ReleaseNotes_Controller.md with know issues of R01
    Changed SMD button JLC order number to version without mounting holes
2025-05-11 WIP for R00/R01 hardware
2025-07-20 Add missing osc_logo.h header file
    Set library dependencies to fixed versions
2025-07-20 Added Vext to config
    Manually integrated changes for HW R0/R1
2025-07-30 feat: add honk function for simultaneous B4 and B5 presses
2025-07-30 feat: update honking functionality and clean up button handling
2025-08-23 feat: add toggleResetTime function on extra long press on BTN_3
2025-08-23 refactor: remove debug prints from toggleResetTime function
2025-08-24 Prepare release v1.3.0 (#59)
    * manually merged refactoring branch (issue 6)
    * swithed webserver dependency to use HTTPS instead of SSH
    * swithed webserver dependency to use HTTPS instead of SSH
    * deleted assets folder and changed config
    * Update README.md
    changed theme image link to new assets branch
2025-09-05 Changes for Heltec V3
2025-09-05 Updated ReleaseNotes_Controller
2025-09-06 update controller PCB: wider traces, fix missing trace on V+, add comments, update gerber files (#60)
2025-09-16 controller v3.0 cad design and print files added initially
2025-10-10 feat: add honk volume control to settings and update server handling
2025-10-10 feat: implement channel selection dropdown and update server handling for channel changes
2025-10-10 feat: add start time selection to settings and update server handling for start time changes
2025-10-10 style: enhance settings page layout and improve button aesthetics and mobile use
2025-10-11 fix: update volume and tick mappings for horn and LEDs for improved functionality
2025-11-30 Conerted to KiCad 9 file version.
2026-03-01 add fan grid with screws and seal and led spacers
2026-03-02 Adjusted footprint of mosfets for 0.15mm solder mask spacing
    New Gerber files
2026-03-10 Exclude Symbols from BOM
2026-04-03 added R2 pin config
2026-04-03 pinned ElegantOTA version to omit build error
2026-04-03 init SPI corretly, fix PWM_OE pin, add debug logs
2026-04-28 Feat/honk volume control (#61)
    * feat: add honk volume control and move honking logic to controller
    * feat: add honk volume control to settings and update server handling
    * feat: implement channel selection dropdown and update server handling for channel changes
    * style: update settings page design for improved aesthetics and usability
    * feat: add start time selection to settings and update server handling for start time changes
    * style: enhance settings page layout and improve button aesthetics and mobile use
2026-04-28 FIX: potential race condition with LoRa RX flag beeing reset after handling message.
    When a message is received during the processing of the last message, the flag will be reset before handling the new message.
    This depends on radio config and build settings.
2026-05-01 Add parameter to Horn constructor for different HW configurations
2026-05-08 FIX: Button 4/5 were handled two times
2026-05-09 Restructuring of Controller Code
    WIP
    Introduced ShotClockLogic class
2026-05-10 Restructuring of Controller Code
    WIP
    platformio.ini:
    - removed lib_deps to heltec dev-boards
    Moved display functions to ShotClockUI
    - integrated setDataDisplay, setPauseDisplay, honk
    - added new telemetry data UI with ID, Battery and RSSI
2026-05-15 Added new Link Layer classes:
    - SCLink
    - ControllerLink
    - DisplayLink
    WIP
2026-05-16 Created DisplayLogic
    Introduced Interface classes for interaction between layers
    WIP
2026-05-17 Implemented RSSI and Battery voltage in telemetry data
    Implemented basic ID assignment
    Add confirmed devices to list
    SCLink:
    - added getRSSI()
    - added priority flag to protocol_t to insert in front of list
    - added some more logic to the state machine
2026-05-17 SCLink, ControllerLink, DisplayLink
    - use protocol_t for data transfer in functions
    - show ID after setID command
    ShotClockLogic:
    - fixed timings in pause mode
    - changed handling of telemetry command and response
    LEDs:
